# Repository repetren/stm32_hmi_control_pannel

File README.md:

# STM32 CAN Dashboard Panel

Control unit for generating CAN signals based on an STM32. Inputs from magnetic encoders, buttons, and a potentiometer.

My personal project with goal to expand my knowledge about industry standards communication protocols.

Created to provide interactive demo CAN inputs for my [Motorcycle Instrument Cluster project](https://github.com/repetren/moto_instrument_cluster).

### [Watch demo and work in progress video on YouTube](https://youtu.be/6McVTvd34ow)

### Features:
- Timers for CAN frame transmission schedule  
- Buttons via EXTI
- Software button debounce
- LED indicators for power and mode indicators
- Two potentiometer modes for two CAN frames
- ADC with DMA for potentiometer sampling

### Power and ESD
- 5 V input, 3.3 V logic. Conversion through LD1117A regulator
- TVS diode for CAN bus and power input protection

## Project Structure

I'm using **[app.c](App/Src/app.c)** to avoid deal with USER CODE BLOCKs inside STM32 generated code.

**CAN_Control_Panel**

App:
- Inc - Header
- Src - Source - **main [app.c](App/Src/app.c)**

Core: Startup + HAL init (generated)
- Inc
- Src - **main.c** contains **app.c**

Docs:
- CAN message map

Hardware:
- PCB - Gerbers, BOM, circuit diagram
- 3DPrints - Knobs, buttons, frame .stl files

## Hardware
- STM32F446RET6 as main MCU
- 6 push buttons via EXTI interrupts
- 2 rotary encoders (AS5048B) over I2C
- 1 potentiometer with analog input
- CAN transceiver: SN65HVD230DR
- UART for debugging and serial output
- SWD interface for firmware flashing and debugging

## Software Architecture

The panel collects input data from physical controls and sensors, processes them periodically in the main loop, and sends formatted messages over CAN and UART.

| Input                     | Interface       | Processed in            | Purpose                                    |
| :-----------------------: | --------------- | ----------------------- | ------------------------------------------ |
| Buttons (6 pcs)           | EXTI interrupts | EXTI + Debounce.        | Gear, turn signals, potentiometer modes    |
| Magnetic encoders (2 pcs) | I2C             | `[encoder_remap](App/Src/encoder_utils.c)`       | Angle to telemetry parameter               |
| Potentiometer             | ADC + DMA       | `[fuel_and_temp_utils.c](App/Src/fuel_and_temp_utils.c)` | Fuel/temperature input (depending on mode) |

#### Periodic task handling ([app.c](App/Src/app.c))
Tasks are executed based on timing from the TIM14 timer.

|  Frequency | Task responsibilities                                                                                 |
| :--------: | --------------------------------------------------------------------------------                      |
| **100 Hz** | Update telemetry, monitor temperature, send telemetry                                                 |
|  **50 Hz** | Update lights and send over CAN light frame                                                           |
|  **25 Hz** | Fuel conversion, range estimation, vehicle info broadcast, low fuel notification, CAN fuel frame send |

#### Output communication

| Output  | Used for                                                                                  |
| ------- | --------------------------------------------------------------------                      |
| UART    | Debug messages                                                                            |
| CAN bus | Telemetry, light control, fuel, and notification frames sent to Raspberry Pi with CAN HAT |

## CAN Frame Map

## Build and run

### Requirements
 - VS Code
 - Installed [STM32CubeIDE for Visual Studio Code](https://marketplace.visualstudio.com/items?itemName=stmicroelectronics.stm32-vscode-extension)
 - [STLINK-V3MINIE](https://www.digikey.de/de/products/detail/stmicroelectronics/STLINK-V3MINIE/16284301)

### VS Code
1. Open repository folder
2. Configure project. CMD (CTRL) + Shift + P
```
Setup STM32Cube project(s)
```

3. Select device

4. Click "Save and close"

5. Run and debug

6. Select ST-LINK server

7. Select project .elf

8. Click "Continue" (F5)

## Future improvements
- Replacing big SWD 14-pin connector to 6-pin version

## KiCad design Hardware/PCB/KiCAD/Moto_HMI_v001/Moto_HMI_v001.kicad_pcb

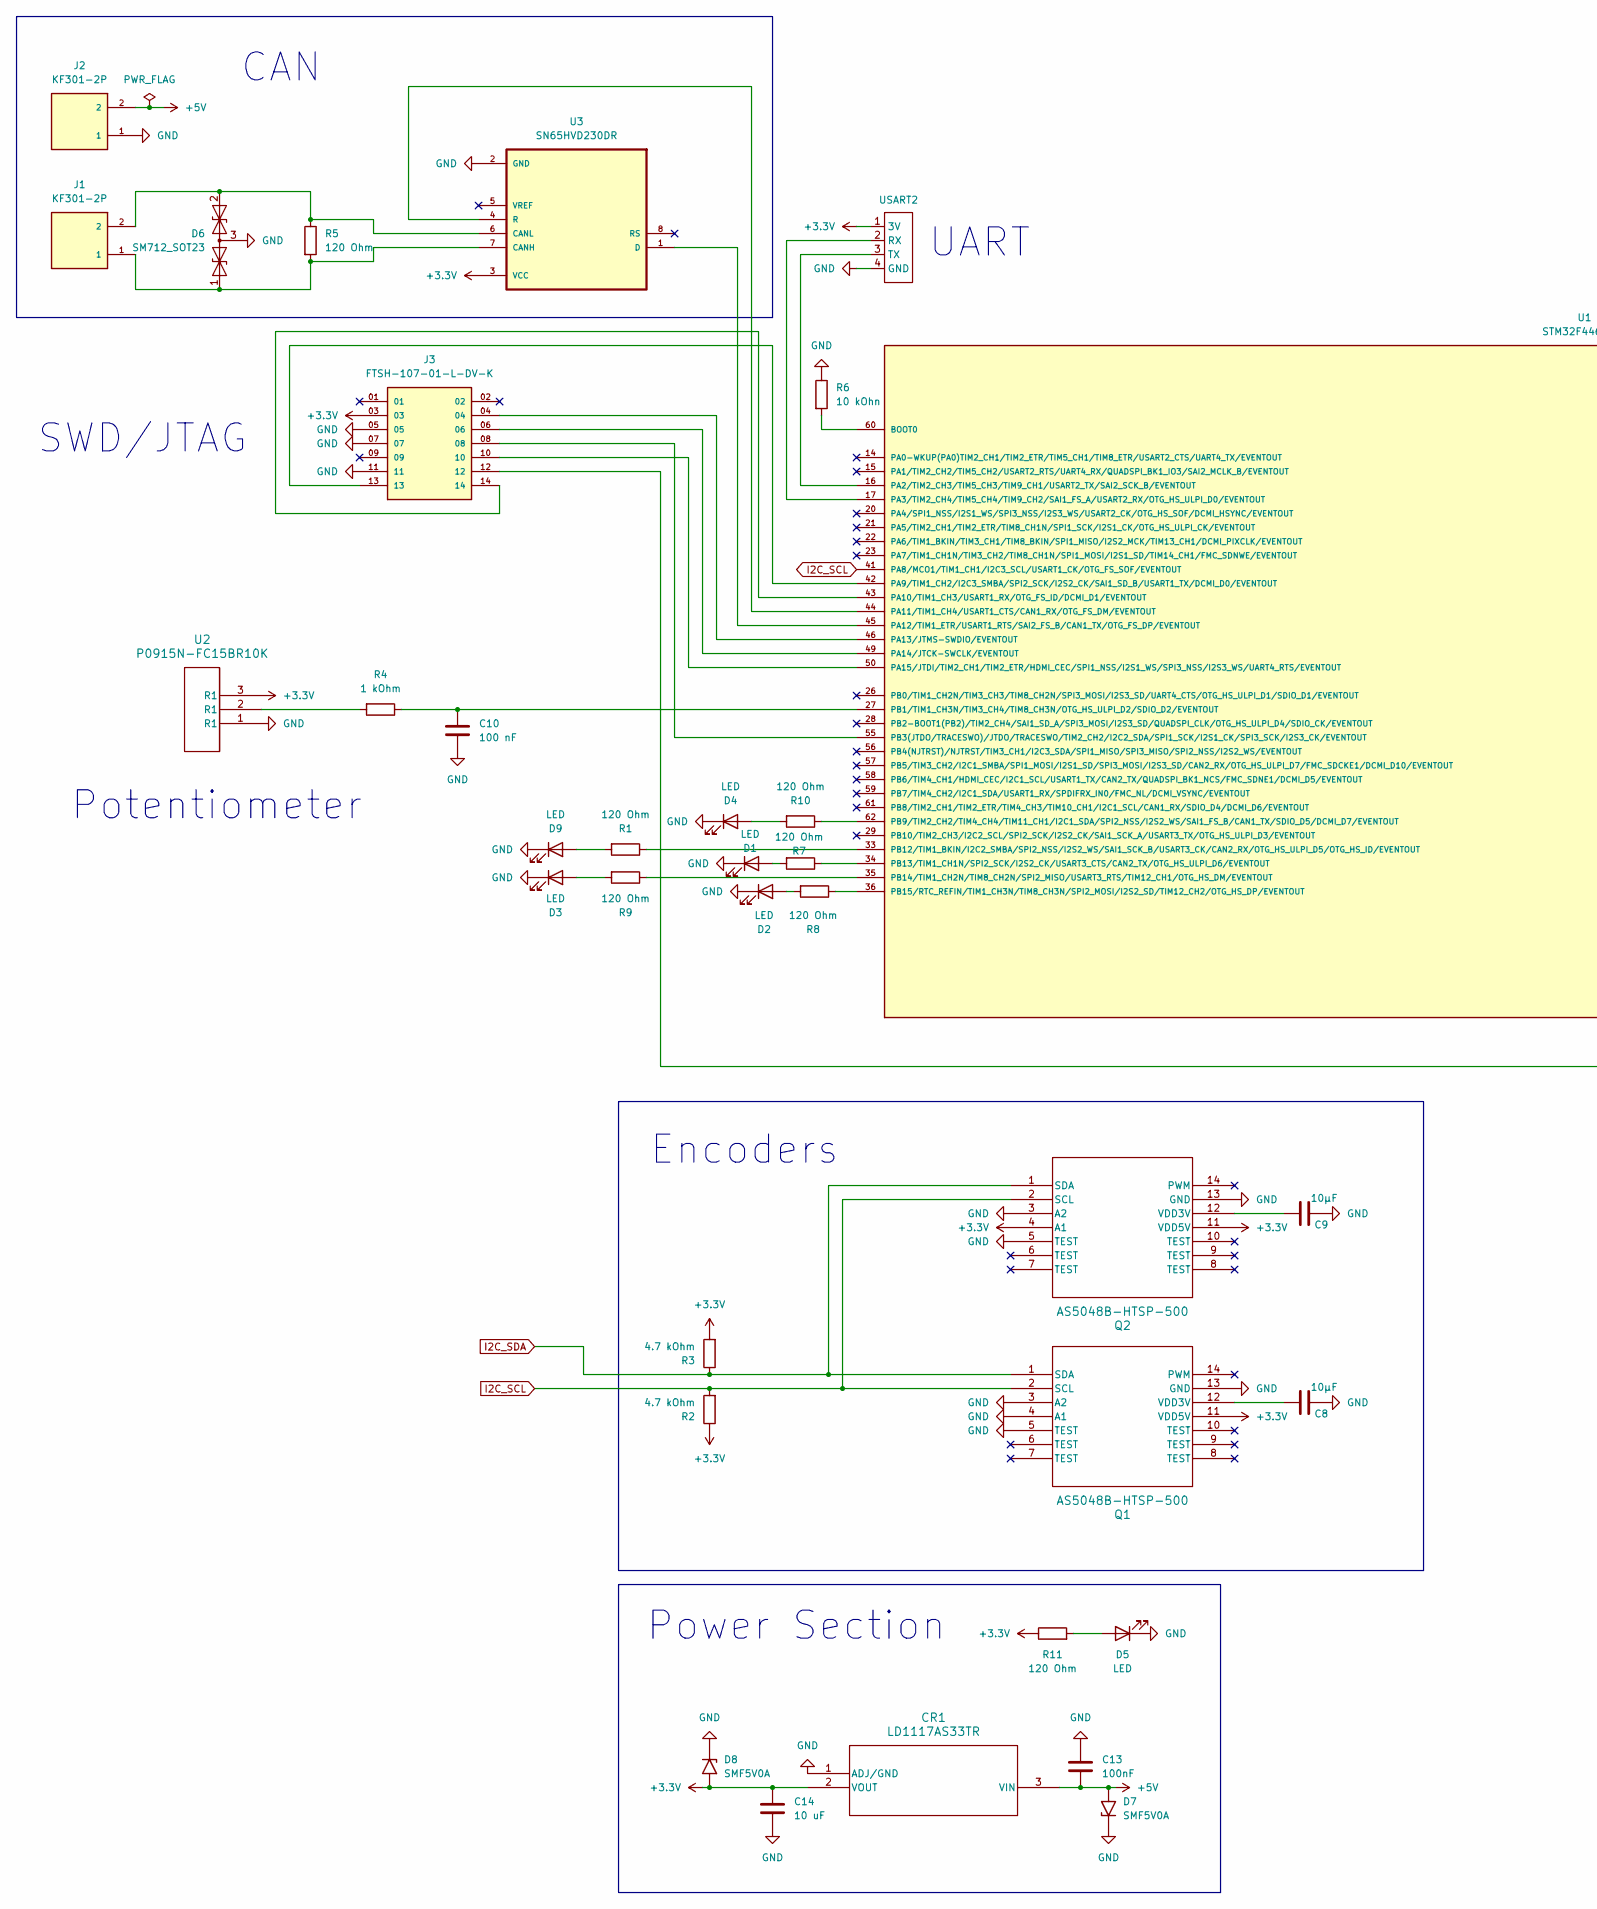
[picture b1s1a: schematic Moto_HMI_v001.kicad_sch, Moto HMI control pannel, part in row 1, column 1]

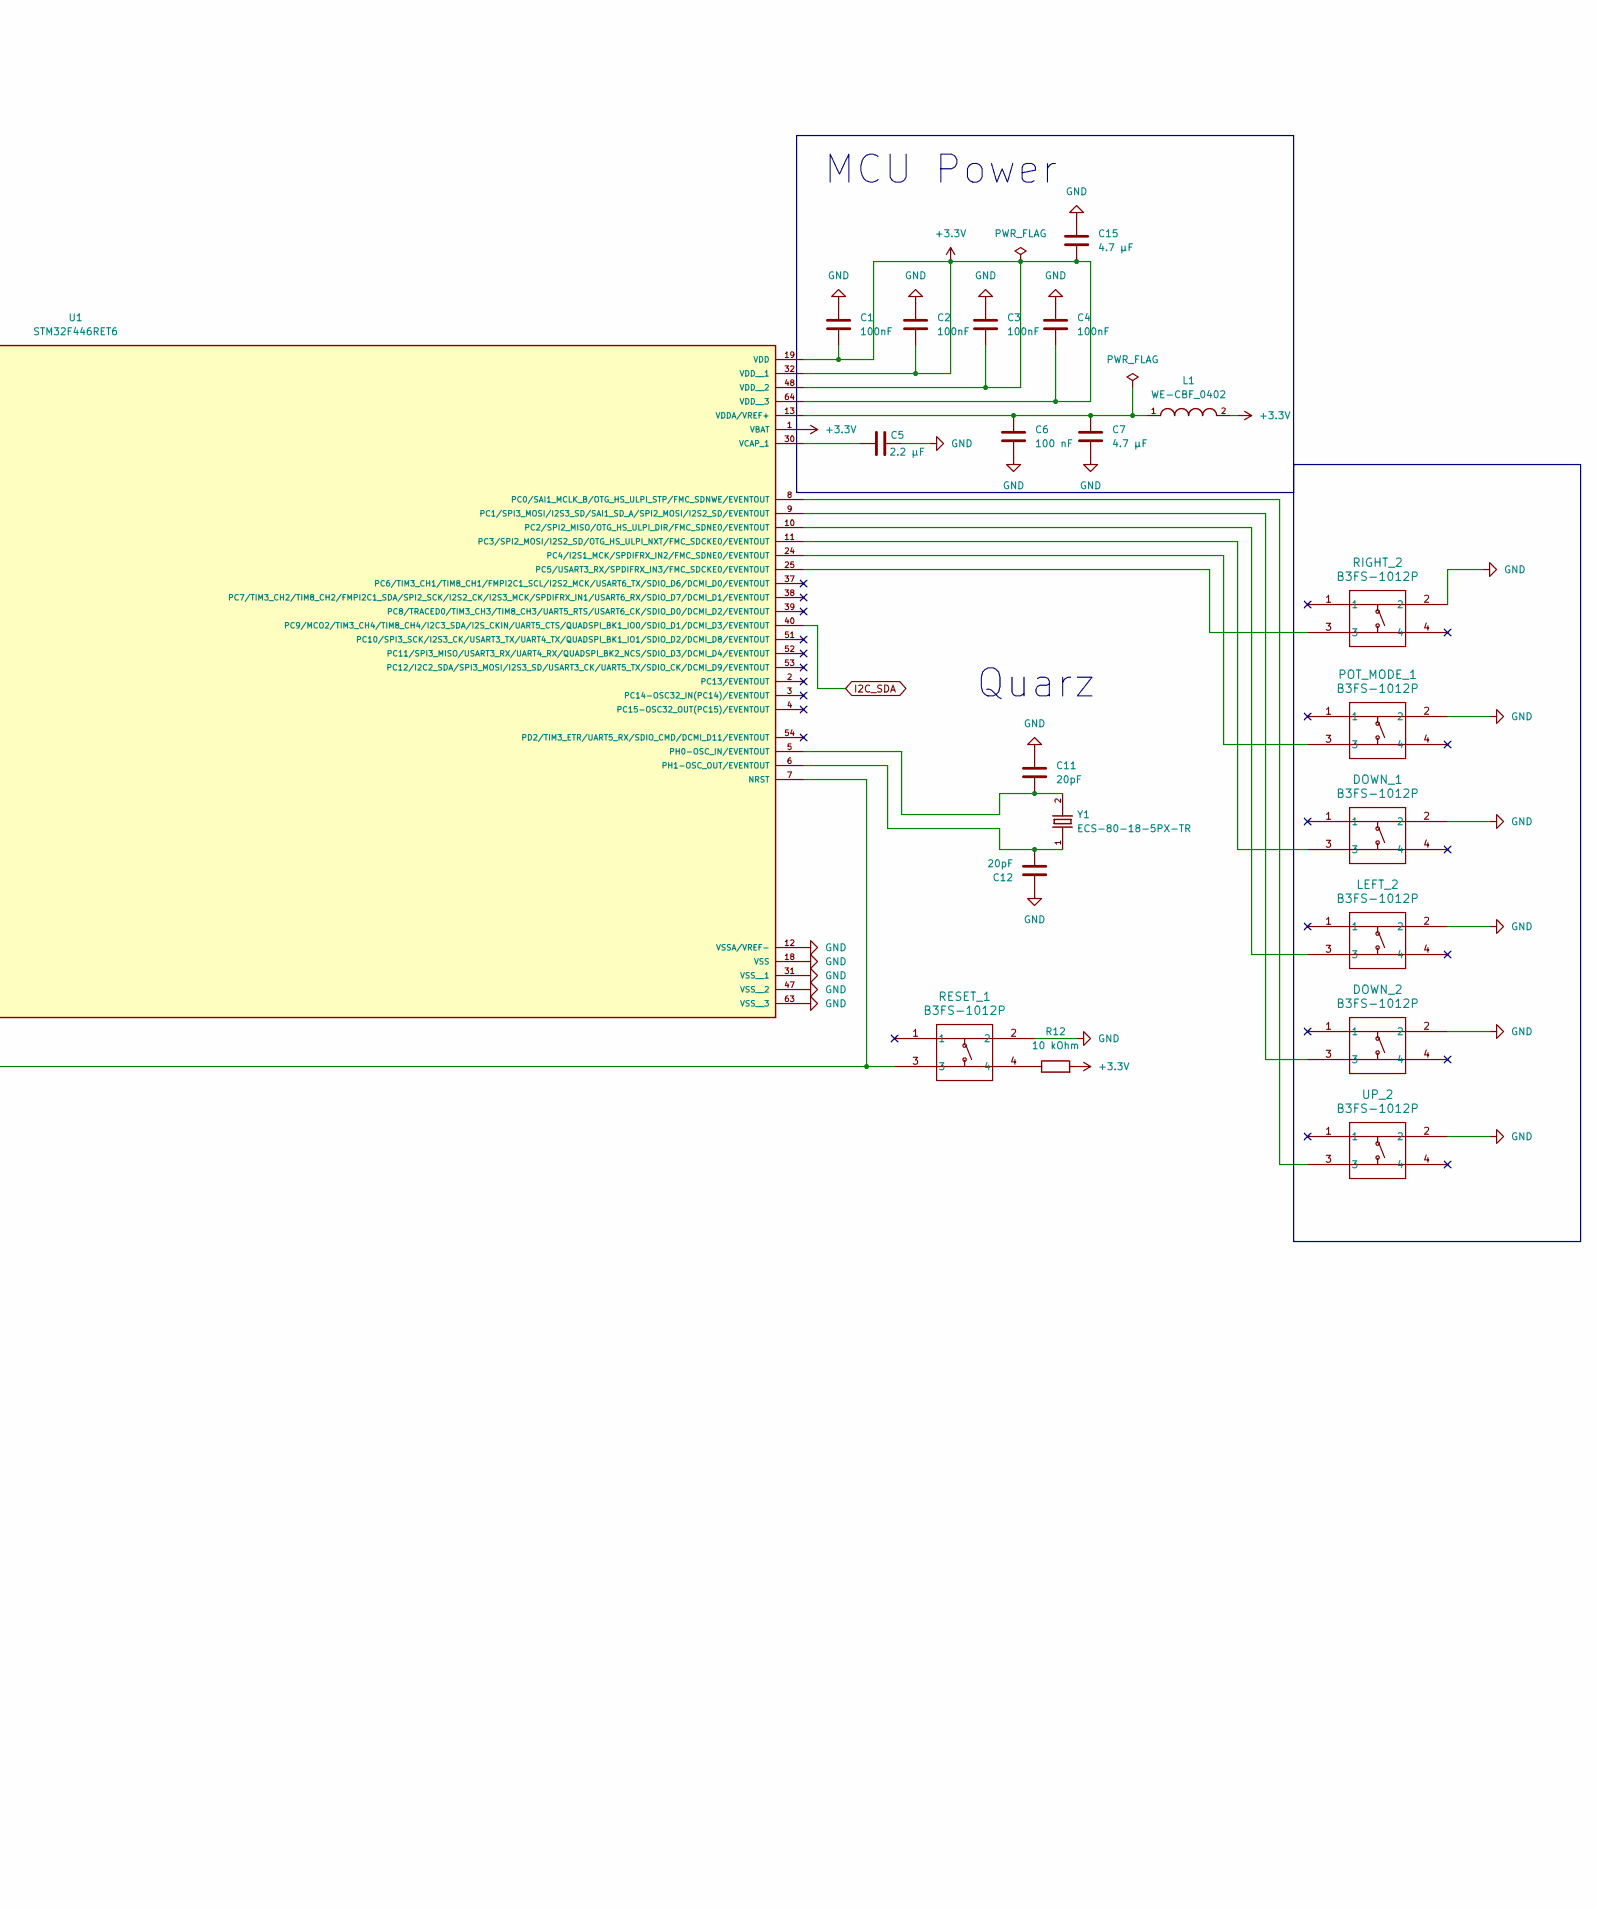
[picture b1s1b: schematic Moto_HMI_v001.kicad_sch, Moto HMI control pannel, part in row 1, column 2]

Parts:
C1, C2, C3, C4, C13: 100nF; CAPC1005X55N
C5: 2.2 µF; C_0402_1005Metric
C6, C10: 100 nF; CAPC1005X55N
C7, C15: 4.7 µF; CAPC1608X90N
C8, C9: 10μF; CAPC1608X90N
C11, C12: 20pF; CAPC17595_87N_KEM
C14: 10 uF; CAPC1608X90N
CR1: LD1117AS33TR; SOT-223_STM
D1, D2, D3, D4, D5, D9: LED; LED_1206_3216Metric
D6: SM712_SOT23; SOT-23
D7, D8: SMF5V0A; D_SMF
DOWN_1, DOWN_2: B3FS-1012P; B3FS-101_OMR
J1, J2: KF301-2P; HANDSON_KF301-2P; PARTREV NA
J3: FTSH-107-01-L-DV-K; SAMTEC_FTSH-107-01-L-DV-K; PARTREV R
L1: WE-CBF_0402; WE-CBF_0402_W1.5
LEFT_2: B3FS-1012P; B3FS-101_OMR
POT_MODE_1: B3FS-1012P; B3FS-101_OMR
Q1, Q2: AS5048B-HTSP-500; TRANS_HTSP-500_AMS-M
R1, R5, R7, R8, R9, R10, R11: 120 Ohm; R_0603_1608Metric
R2, R3: 4.7 kOhm; R_0603_1608Metric
R4: 1 kOhm; R_0603_1608Metric
R6: 10 kOhn; R_0603_1608Metric
R12: 10 kOhm; R_0603_1608Metric
RESET_1: B3FS-1012P; B3FS-101_OMR
RIGHT_2: B3FS-1012P; B3FS-101_OMR
U1: STM32F446RET6; QFP50P1200X1200X160-64N; PARTREV 6
U2: P0915N-FC15BR10K; SWITCH_C15BR10K_BIT
U3: SN65HVD230DR; SOIC127P599X175-8N
UP_2: B3FS-1012P; B3FS-101_OMR
USART2: PinHeader_1x04_P2.54mm_Vertical
Y1: ECS-80-18-5PX-TR; XTAL_ECS-80-18-5PX-TR; PARTREV 2017

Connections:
+3.3V: C1.2, C2.2, C3.2, C4.2, C14.1, C15.2, CR1.2 (VOUT), D8.2 (A2), J3.03, L1.2, Q1.11 (VDD5V), Q2.4 (A1), Q2.11 (VDD5V), R2.1, R3.2, R11.1, R12.2, U1.1 (VBAT), U1.19 (VDD), U1.32 (VDD__1), U1.48 (VDD__2), U1.64 (VDD__3), U2.3 (R1), U3.3 (VCC), USART2.1 (3V)
+5V: C13.2, CR1.3 (VIN), D7.2 (A2), J2.2
GND: C1.1, C2.1, C3.1, C4.1, C5.1, C6.2, C7.2, C8.2, C9.2, C10.2, C11.1, C12.1, C13.1, C14.2, C15.1, CR1.1 (ADJ/GND), D1.1 (K), D2.1 (K), D3.1 (K), D4.1 (K), D5.1 (K), D6.3 (common), D7.1 (A1), D8.1 (A1), D9.1 (K), DOWN_1.2, DOWN_2.2, J2.1, J3.05, J3.07, J3.11, LEFT_2.2, POT_MODE_1.2, Q1.3 (A2), Q1.4 (A1), Q1.5 (TEST), Q1.13 (GND), Q2.3 (A2), Q2.5 (TEST), Q2.13 (GND), R6.1, RESET_1.2, RIGHT_2.2, U1.12 (VSSA/VREF-), U1.18 (VSS), U1.31 (VSS__1), U1.47 (VSS__2), U1.63 (VSS__3), U2.1 (R1), U3.2 (GND), UP_2.2, USART2.4 (GND); also elsewhere on the board
I2C_SCL: Q1.2 (SCL), Q2.2 (SCL), R2.2, U1.41 (PA8/MCO1/TIM1_CH1/I2C3_SCL/USART1_CK/OT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)
I2C_SDA: Q1.1 (SDA), Q2.1 (SDA), R3.1, U1.40 (PC9/MCO2/TIM3_CH4/TIM8_CH4/I2C3_SDA/I2S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)
unnamed: D1.2 (A), R7.2
unnamed: D2.2 (A), R8.2
unnamed: D3.2 (A), R9.2
unnamed: D4.2 (A), R10.2
unnamed: D5.2 (A), R11.2
unnamed: D6.1 (A1), J1.1, R5.2, U3.7 (CANH)
unnamed: D6.2 (A2), J1.2, R5.1, U3.6 (CANL)
unnamed: D9.2 (A), R1.2
unnamed: C8.1, Q1.12 (VDD3V)
unnamed: C9.1, Q2.12 (VDD3V)
unnamed: R4.2, U2.2 (R1)
unnamed: R12.1, RESET_1.4
unnamed: R6.2, U1.60 (BOOT0)
unnamed: J3.12, RESET_1.3, U1.7 (NRST)
unnamed: U1.16 (PA2/TIM2_CH3/TIM5_CH3/TIM9_CH1/USART2_T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), USART2.3 (TX)
unnamed: U1.17 (PA3/TIM2_CH4/TIM5_CH4/TIM9_CH2/SAI1_FS_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), USART2.2 (RX)
unnamed: J3.13, U1.42 (PA9/TIM1_CH2/I2C3_SMBA/SPI2_SCK/I2S2_CK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)
unnamed: J3.14, U1.43 (PA10/TIM1_CH3/USART1_RX/OTG_FS_ID/DCMI_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)
unnamed: U1.44 (PA11/TIM1_CH4/USART1_CTS/CAN1_RX/OTG_FS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), U3.4 (R)
unnamed: U1.45 (PA12/TIM1_ETR/USART1_RTS/SAI2_FS_B/CAN1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), U3.1 (D)
unnamed: J3.04, U1.46 (PA13/JTMS-SWDIO/EVENTOUT)
unnamed: J3.06, U1.49 (PA14/JTCK-SWCLK/EVENTOUT)
unnamed: J3.10, U1.50 (PA15/JTDI/TIM2_CH1/TIM2_ETR/HDMI_CEC/SP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)
unnamed: C10.1, R4.1, U1.27 (PB1/TIM1_CH3N/TIM3_CH4/TIM8_CH3N/OTG_HS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)
unnamed: J3.08, U1.55 (PB3(JTDO/TRACESWO)/JTDO/TRACESWO/TIM2_C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)
unnamed: R10.1, U1.62 (PB9/TIM2_CH2/TIM4_CH4/TIM11_CH1/I2C1_SD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)
unnamed: R1.1, U1.33 (PB12/TIM1_BKIN/I2C2_SMBA/SPI2_NSS/I2S2_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)
unnamed: R7.1, U1.34 (PB13/TIM1_CH1N/SPI2_SCK/I2S2_CK/USART3_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)
unnamed: R9.1, U1.35 (PB14/TIM1_CH2N/TIM8_CH2N/SPI2_MISO/USAR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)
unnamed: R8.1, U1.36 (PB15/RTC_REFIN/TIM1_CH3N/TIM8_CH3N/SPI2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)
unnamed: U1.8 (PC0/SAI1_MCLK_B/OTG_HS_ULPI_STP/FMC_SDN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), UP_2.3
unnamed: DOWN_2.3, U1.9 (PC1/SPI3_MOSI/I2S3_SD/SAI1_SD_A/SPI2_MO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)
unnamed: LEFT_2.3, U1.10 (PC2/SPI2_MISO/OTG_HS_ULPI_DIR/FMC_SDNE0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)
unnamed 38: DOWN_1.3, U1.11 (PC3/SPI2_MOSI/I2S2_SD/OTG_HS_ULPI_NXT/F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); also elsewhere on the board
unnamed: POT_MODE_1.3, U1.24 (PC4/I2S1_MCK/SPDIFRX_IN2/FMC_SDNE0/EVEN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)
unnamed: RIGHT_2.3, U1.25 (PC5/USART3_RX/SPDIFRX_IN3/FMC_SDCKE0/EV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)
unnamed: C11.2, U1.5 (PH0-OSC_IN/EVENTOUT), Y1.2
unnamed: C12.2, U1.6 (PH1-OSC_OUT/EVENTOUT), Y1.1
unnamed: C5.2, U1.30 (VCAP_1)
unnamed: C6.1, C7.1, L1.1, U1.13 (VDDA/VREF+)

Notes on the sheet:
Encoders
Quarz
SWD/JTAG
Power Section
UART
MCU Power
CAN
Potentiometer

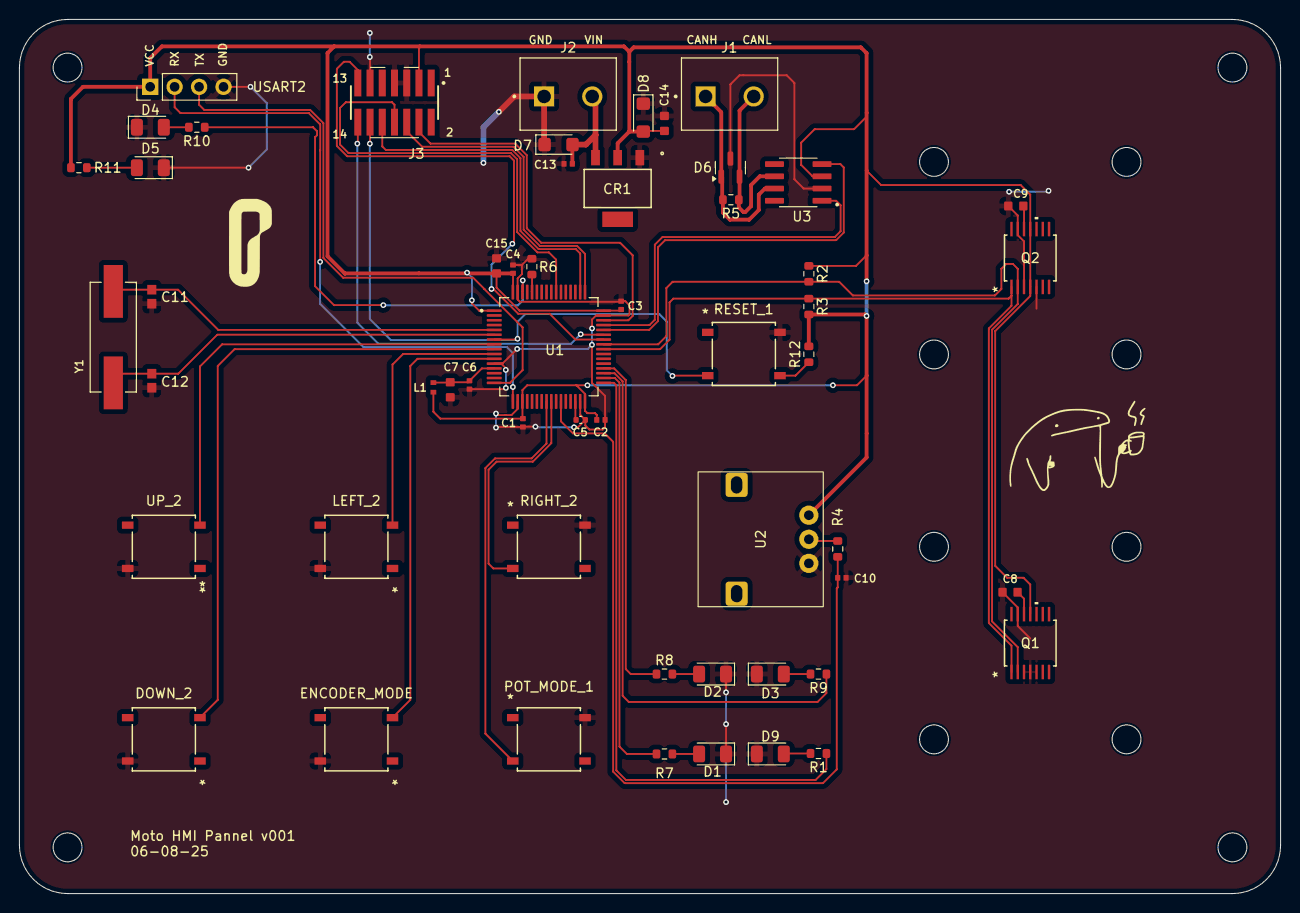
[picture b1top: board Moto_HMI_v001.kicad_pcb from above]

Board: 4 copper layers, 131.0 x 90.8 mm, 55 parts (0 on the bottom side), 45 nets.

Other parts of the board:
ENCODER_MODE  : B3FS-1012P; B3FS-101_OMR

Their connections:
GND: ENCODER_MODE.2; also elsewhere on the board
unnamed 38: ENCODER_MODE.3; also elsewhere on the board

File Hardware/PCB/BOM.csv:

"Reference","Qty","Value","DNP","Exclude from BOM","Exclude from Board","Footprint","Datasheet"
"C1,C2,C3,C4,C13","5","100nF","","","","CL05B104KP5NNNC:CAPC1005X55N","~"
"C5","1","2.2 µF","","","","Capacitor_SMD:C_0402_1005Metric","~"
"C6,C10","2","100 nF","","","","CL05B104KP5NNNC:CAPC1005X55N","~"
"C7,C15","2","4.7 µF","","","","CL10A475KP8NNNC:CAPC1608X90N","~"
"C8,C9","2","10μF","","","","CL10A106KQ8NNNC:CAPC1608X90N","~"
"C11,C12","2","20pF","","","","C0603C200G8HACTU:CAPC17595_87N_KEM","~"
"C14","1","10 uF","","","","CL10A106KQ8NNNC:CAPC1608X90N","~"
"CR1","1","LD1117AS33TR","","","","LD1117AS33TR:SOT-223_STM","https://www.st.com/resource/en/datasheet/ld1117a.pdf"
"D1,D2,D3,D4,D5,D9","6","LED","","","","LED_SMD:LED_1206_3216Metric","~"
"D6","1","SM712_SOT23","","","","Package_TO_SOT_SMD:SOT-23","https://www.littelfuse.com/~/media/electronics/datasheets/tv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"
"D7,D8","2","SMF5V0A","","","","Diode_SMD:D_SMF","https://www.vishay.com/doc?85881"
"DOWN_1,DOWN_2,LEFT_2,POT_MODE_1,RESET_1,RIGHT_2,UP_2","7","B3FS-1012P","","","","B3FS_1012P:B3FS-101_OMR","B3FS-1012P"
"J1,J2","2","KF301-2P","","","","KF301-2P:HANDSON_KF301-2P",""
"J3","1","FTSH-107-01-L-DV-K","","","","FTSH_107_01_L_DV_K:SAMTEC_FTSH-107-01-L-DV-K",""
"L1","1","WE-CBF_0402","","","","74279271:WE-CBF_0402_W1.5",""
"Q1,Q2","2","AS5048B-HTSP-500","","","","AS5048B-HTSP-500:TRANS_HTSP-500_AMS-M","AS5048B-HTSP-500"
"R1,R5,R7,R8,R9,R10,R11","7","120 Ohm","","","","Resistor_SMD:R_0603_1608Metric","~"
"R2,R3","2","4.7 kOhm","","","","Resistor_SMD:R_0603_1608Metric","~"
"R4","1","1 kOhm","","","","Resistor_SMD:R_0603_1608Metric","~"
"R6","1","10 kOhn","","","","Resistor_SMD:R_0603_1608Metric","~"
"R12","1","10 kOhm","","","","Resistor_SMD:R_0603_1608Metric","~"
"U1","1","STM32F446RET6","","","","STM32F446RET6:QFP50P1200X1200X160-64N",""
"U2","1","P0915N-FC15BR10K","","","","P0915N_FC15BR10K:SWITCH_C15BR10K_BIT","P0915N-FC15BR10K"
"U3","1","SN65HVD230DR","","","","SN65HVD230DR:SOIC127P599X175-8N",""
"USART2","1","~","","","","Connector_PinHeader_2.54mm:PinHeader_1x04_P2.54mm_Vertical",""
"Y1","1","ECS-80-18-5PX-TR","","","","ECS_80_18_5PX_TR:XTAL_ECS-80-18-5PX-TR",""

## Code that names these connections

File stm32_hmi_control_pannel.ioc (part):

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Mcu.Name=STM32F446R(C-E)Tx
Mcu.Package=LQFP64
Mcu.UserName=STM32F446RETx
PA11.Mode=CAN_Activate
PA11.Signal=CAN1_RX
PA12.Mode=CAN_Activate
PA12.Signal=CAN1_TX
PA13.Mode=Serial_Wire
PA13.Signal=SYS_JTMS-SWDIO
PA14.Mode=Serial_Wire
PA14.Signal=SYS_JTCK-SWCLK
PA2.Mode=Asynchronous
PA2.Signal=USART2_TX
PA3.Mode=Asynchronous
PA3.Signal=USART2_RX
PA8.Mode=I2C
PA8.Signal=I2C3_SCL
PB1.Signal=ADCx_IN9
PB14.GPIOParameters=GPIO_Label
PB14.GPIO_Label=LED_2
PB14.Signal=GPIO_Output
PB15.GPIOParameters=GPIO_Label
PB15.GPIO_Label=LED_1
PB15.Signal=GPIO_Output
PC0.GPIOParameters=GPIO_PuPd,GPIO_Label,GPIO_ModeDefaultEXTI
PC0.GPIO_Label=BTN_UP
PC0.GPIO_ModeDefaultEXTI=GPIO_MODE_IT_FALLING
PC0.GPIO_PuPd=GPIO_PULLUP
PC0.Signal=GPXTI0
PC1.GPIOParameters=GPIO_PuPd,GPIO_Label,GPIO_ModeDefaultEXTI
PC1.GPIO_Label=BTN_DOWN
PC1.GPIO_ModeDefaultEXTI=GPIO_MODE_IT_FALLING
PC1.GPIO_PuPd=GPIO_PULLUP
PC1.Signal=GPXTI1
PC2.GPIOParameters=GPIO_PuPd,GPIO_Label,GPIO_ModeDefaultEXTI
PC2.GPIO_Label=BTN_LEFT
PC2.GPIO_ModeDefaultEXTI=GPIO_MODE_IT_FALLING
PC2.GPIO_PuPd=GPIO_PULLUP
PC2.Signal=GPXTI2
PC3.GPIOParameters=GPIO_PuPd,GPIO_Label,GPIO_ModeDefaultEXTI
PC3.GPIO_Label=LIGHT_MODE
PC3.GPIO_ModeDefaultEXTI=GPIO_MODE_IT_FALLING
PC3.GPIO_PuPd=GPIO_PULLUP
PC3.Signal=GPXTI3
PC4.GPIOParameters=GPIO_PuPd,GPIO_Label,GPIO_ModeDefaultEXTI
PC4.GPIO_Label=BTN_POT_MODE
PC4.GPIO_ModeDefaultEXTI=GPIO_MODE_IT_FALLING
PC4.GPIO_PuPd=GPIO_PULLUP
PC4.Signal=GPXTI4
PC5.GPIOParameters=GPIO_PuPd,GPIO_Label,GPIO_ModeDefaultEXTI
PC5.GPIO_Label=BTN_RIGHT
PC5.GPIO_ModeDefaultEXTI=GPIO_MODE_IT_FALLING
PC5.GPIO_PuPd=GPIO_PULLUP
PC5.Signal=GPXTI5
PC9.Mode=I2C
PC9.Signal=I2C3_SDA
PH0-OSC_IN.Mode=HSE-External-Oscillator
PH0-OSC_IN.Signal=RCC_OSC_IN
PH1-OSC_OUT.Mode=HSE-External-Oscillator
PH1-OSC_OUT.Signal=RCC_OSC_OUT
RCC.HSE_VALUE=8000000
RCC.SYSCLKFreq_VALUE=180000000
RCC.SYSCLKSource=RCC_SYSCLKSOURCE_PLLRCLK
board=custom

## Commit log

2025-09-21 Add all buttons, encoders, potentiometer, and LEDs
2025-09-21 Add DAM, separate code for functions
2025-09-23 Add CAN trasmition v0
2025-09-24 Distribute CAN frames for dedicated frequences
2025-09-28 Add notification handler and odometer
2025-11-02 Extract CAN to separate file
2025-11-02 Throw out ignored garbage
2025-11-02 Clean code
